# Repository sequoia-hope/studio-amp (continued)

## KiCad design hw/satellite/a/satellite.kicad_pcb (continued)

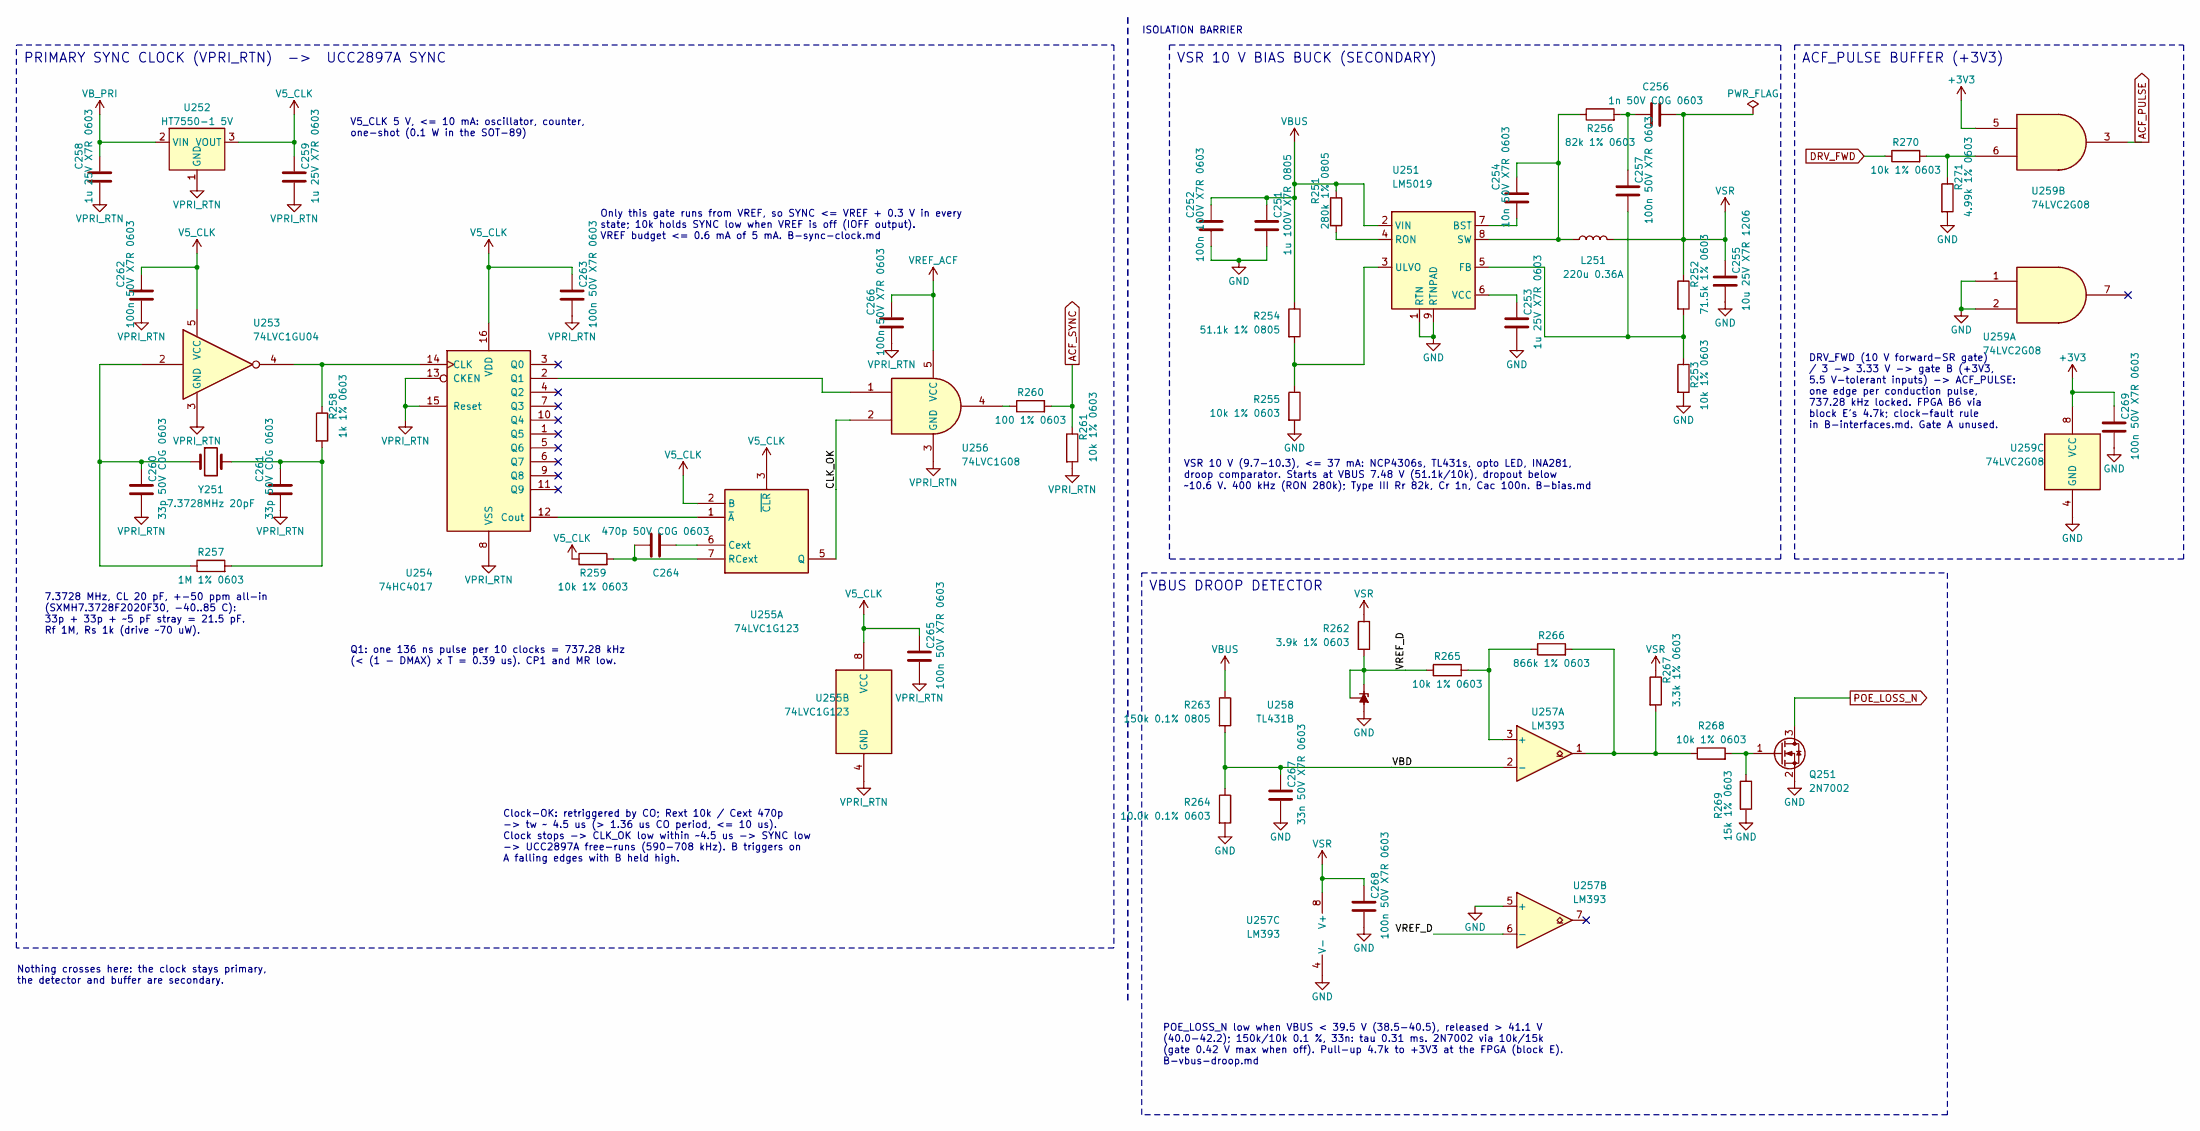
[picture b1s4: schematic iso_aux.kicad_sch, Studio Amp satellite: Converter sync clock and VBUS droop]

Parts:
C251: 1u 100V X7R 0805; C_0805_2012Metric; MPN HMK212BC7105KGHTE; LCSC C385977
C252: 100n 100V X7R 0603; C_0603_1608Metric; MPN CL10B104KC8NNNC; LCSC C15725
C253, C258, C259: 1u 25V X7R 0603; C_0603_1608Metric; MPN CL10B105KA8NNNC; LCSC C29936
C254: 10n 50V X7R 0603; C_0603_1608Metric; MPN CL10B103KB8NNNC; LCSC C1589
C255: 10u 25V X7R 1206; C_1206_3216Metric; MPN CL31B106KAHNNNE; LCSC C14860
C256: 1n 50V C0G 0603; C_0603_1608Metric; MPN CL10C102JB8NNNC; LCSC C163508
C257, C262, C263, C265, C266, C268, C269: 100n 50V X7R 0603; C_0603_1608Metric; MPN CL10B104KB8NNNC; LCSC C1591
C260, C261: 33p 50V C0G 0603; C_0603_1608Metric; MPN CL10C330JB8NNNC; LCSC C1663
C264: 470p 50V C0G 0603; C_0603_1608Metric; MPN CL10C471JB8NNNC; LCSC C27694
C267: 33n 50V X7R 0603; C_0603_1608Metric; MPN CL10B333KB8NNNC; LCSC C21117
L251: 220u 0.36A; L_SXN_SM5845; MPN SM5845-221MT; LCSC C10123
Q251: 2N7002; SOT-23; MPN 2N7002; LCSC C8545
R251: 280k 1% 0805; R_0805_2012Metric; MPN 0805W8F2803T5E; LCSC C17597
R252: 71.5k 1% 0603; R_0603_1608Metric; MPN 0603WAF7152T5E; LCSC C23103
R253, R255, R259, R261, R265, R268, R270: 10k 1% 0603; R_0603_1608Metric; MPN 0603WAF1002T5E; LCSC C25804
R254: 51.1k 1% 0805; R_0805_2012Metric; MPN 0805W8F5112T5E; LCSC C17731
R256: 82k 1% 0603; R_0603_1608Metric; MPN 0603WAF8202T5E; LCSC C23254
R257: 1M 1% 0603; R_0603_1608Metric; MPN 0603WAF1004T5E; LCSC C22935
R258: 1k 1% 0603; R_0603_1608Metric; MPN 0603WAF1001T5E; LCSC C21190
R260: 100 1% 0603; R_0603_1608Metric; MPN 0603WAF1000T5E; LCSC C22775
R262: 3.9k 1% 0603; R_0603_1608Metric; MPN 0603WAF3901T5E; LCSC C23018
R263: 150k 0.1% 0805; R_0805_2012Metric; MPN RT0805BRD07150KL; LCSC C136927
R264: 10.0k 0.1% 0603; R_0603_1608Metric; MPN RT0603BRD0710KL; LCSC C95204
R266: 866k 1% 0603; R_0603_1608Metric; MPN 0603WAF8663T5E; LCSC C23257
R267: 3.3k 1% 0603; R_0603_1608Metric; MPN 0603WAF3301T5E; LCSC C22978
R269: 15k 1% 0603; R_0603_1608Metric; MPN 0603WAF1502T5E; LCSC C22809
R271: 4.99k 1% 0603; R_0603_1608Metric; MPN 0603WAF4991T5E; LCSC C23046
U251: LM5019; SOIC-8-1EP_3.9x4.9mm_P1.27mm_EP2.95x4.9mm_Mask2.71x3.4mm; MPN LM5019MRX/NOPB; LCSC C471034
U252: HT7550-1 5V; SOT-89-3; MPN HT7550-1; LCSC C16106
U253: 74LVC1GU04; SOT-23-5; MPN SN74LVC1GU04DBVR; LCSC C81934
U254: 74HC4017; SOIC-16_3.9x9.9mm_P1.27mm; MPN 74HC4017D,653; LCSC C148206
U255: 74LVC1G123; SSOP-8_2.95x2.8mm_P0.65mm; MPN SN74LVC1G123DCTR; LCSC C123302
U256: 74LVC1G08; SOT-23-5; MPN SN74LVC1G08DBVR; LCSC C7666
U257: LM393; SOIC-8_3.9x4.9mm_P1.27mm; MPN LM393DR2G; LCSC C7955
U258: TL431B; SOT-23; MPN TL431BIDBZR; LCSC C41283
U259: 74LVC2G08; TSSOP-8_3x3mm_P0.65mm; MPN 74LVC2G08DP,125; LCSC C406037
Y251: 7.3728MHz 20pF; Crystal_SMD_HC49-SD; MPN SXMH7.3728F2020F30; LCSC C2901749

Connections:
/iso_aux/CLK_OK: U255.5 (Q), U256.2
/iso_aux/VBD: C267.1, R263.2, R264.1, U257.2 (-)
/iso_aux/VREF_D: R262.2, R265.1, U257.6 (-), U258.1 (K), U258.2 (REF)
ACF_PULSE: U259.3; also elsewhere on the board
ACF_SYNC: R260.2, R261.1; also elsewhere on the board
DRV_FWD: R270.1; also elsewhere on the board
unnamed: C256.1, C257.1, R256.2
unnamed: C260.1, R257.1, U253.2, Y251.1
unnamed: C261.1, R257.2, R258.2, Y251.2
unnamed: Q251.1 (G), R268.2, R269.1
unnamed: R260.1, U256.4
unnamed: R266.2, R267.2, R268.1, U257.1
unnamed: R270.2, R271.1, U259.6
unnamed: C254.2, U251.7 (BST)
unnamed: C257.2, R252.2, R253.1, U251.5 (FB)
unnamed: R251.2, U251.4 (RON)
unnamed: C254.1, L251.1, R256.1, U251.8 (SW)
unnamed: R254.2, R255.1, U251.3 (ULVO)
unnamed: C253.1, U251.6 (VCC)
unnamed: R258.1, U253.4, U254.14 (CLK)
unnamed: U254.12 (Cout), U255.1 (~A)
unnamed: U254.2 (Q1), U256.1
unnamed: C264.2, U255.6 (Cext)
unnamed: C264.1, R259.2, U255.7 (RCext)
unnamed: R265.2, R266.1, U257.3 (+)
POE_LOSS_N: Q251.3 (D); also elsewhere on the board
V5_CLK: C259.1, C262.1, C263.1, C265.1, R259.1, U252.3 (VOUT), U253.5 (VCC), U254.16 (VDD), U255.2 (B), U255.3 (~CLR), U255.8 (VCC)
VPRI_RTN: C258.2, C259.2, C260.2, C261.2, C262.2, C263.2, C265.2, C266.2, R261.2, U252.1 (GND), U253.3 (GND), U254.8 (VSS), U254.13 (CKEN), U254.15 (Reset), U255.4 (GND), U256.3 (GND); also elsewhere on the board
VREF_ACF: C266.1, U256.5 (VCC); also elsewhere on the board
VSR: C255.1, C256.2, C268.1, L251.2, R252.1, R262.1, R267.1, U257.8 (V+); also elsewhere on the board

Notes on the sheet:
V5_CLK 5 V, <= 10 mA: oscillator, counter, one-shot (0.1 W in the SOT-89)
7.3728 MHz, CL 20 pF, +-50 ppm all-in (SXMH7.3728F2020F30, -40..85 C): 33p + 33p + ~5 pF stray = 21.5 pF. Rf 1M, Rs 1k (drive ~70 uW).
Q1: one 136 ns pulse per 10 clocks = 737.28 kHz (< (1 - DMAX) x T = 0.39 us). CP1 and MR low.
Clock-OK: retriggered by CO; Rext 10k / Cext 470p -> tw ~ 4.5 us (> 1.36 us CO period, <= 10 us). Clock stops -> CLK_OK low within ~4.5 us -> SYNC low -> UCC2897A free-runs (590-708 kHz). B triggers on A falling edges with B held high.
Only this gate runs from VREF, so SYNC <= VREF + 0.3 V in every state; 10k holds SYNC low when VREF is off (IOFF output). VREF budget <= 0.6 mA of 5 mA. B-sync-clock.md
PRIMARY SYNC CLOCK (VPRI_RTN) -> UCC2897A SYNC
ISOLATION BARRIER
Nothing crosses here: the clock stays primary, the detector and buffer are secondary.
VSR 10 V (9.7-10.3), <= 37 mA: NCP4306s, TL431s, opto LED, INA281, droop comparator. Starts at VBUS 7.48 V (51.1k/10k), dropout below ~10.6 V. 400 kHz (RON 280k); Type III Rr 82k, Cr 1n, Cac 100n. B-bias.md
VSR 10 V BIAS BUCK (SECONDARY)
POE_LOSS_N low when VBUS < 39.5 V (38.5-40.5), released > 41.1 V (40.0-42.2); 150k/10k 0.1 %, 33n: tau 0.31 ms. 2N7002 via 10k/15k (gate 0.42 V max when off). Pull-up 4.7k to +3V3 at the FPGA (block E). B-vbus-droop.md
VBUS DROOP DETECTOR
DRV_FWD (10 V forward-SR gate) / 3 -> 3.33 V -> gate B (+3V3, 5.5 V-tolerant inputs) -> ACF_PULSE: one edge per conduction pulse, 737.28 kHz locked. FPGA B6 via block E's 4.7k; clock-fault rule in B-interfaces.md. Gate A unused.
ACF_PULSE BUFFER (+3V3)

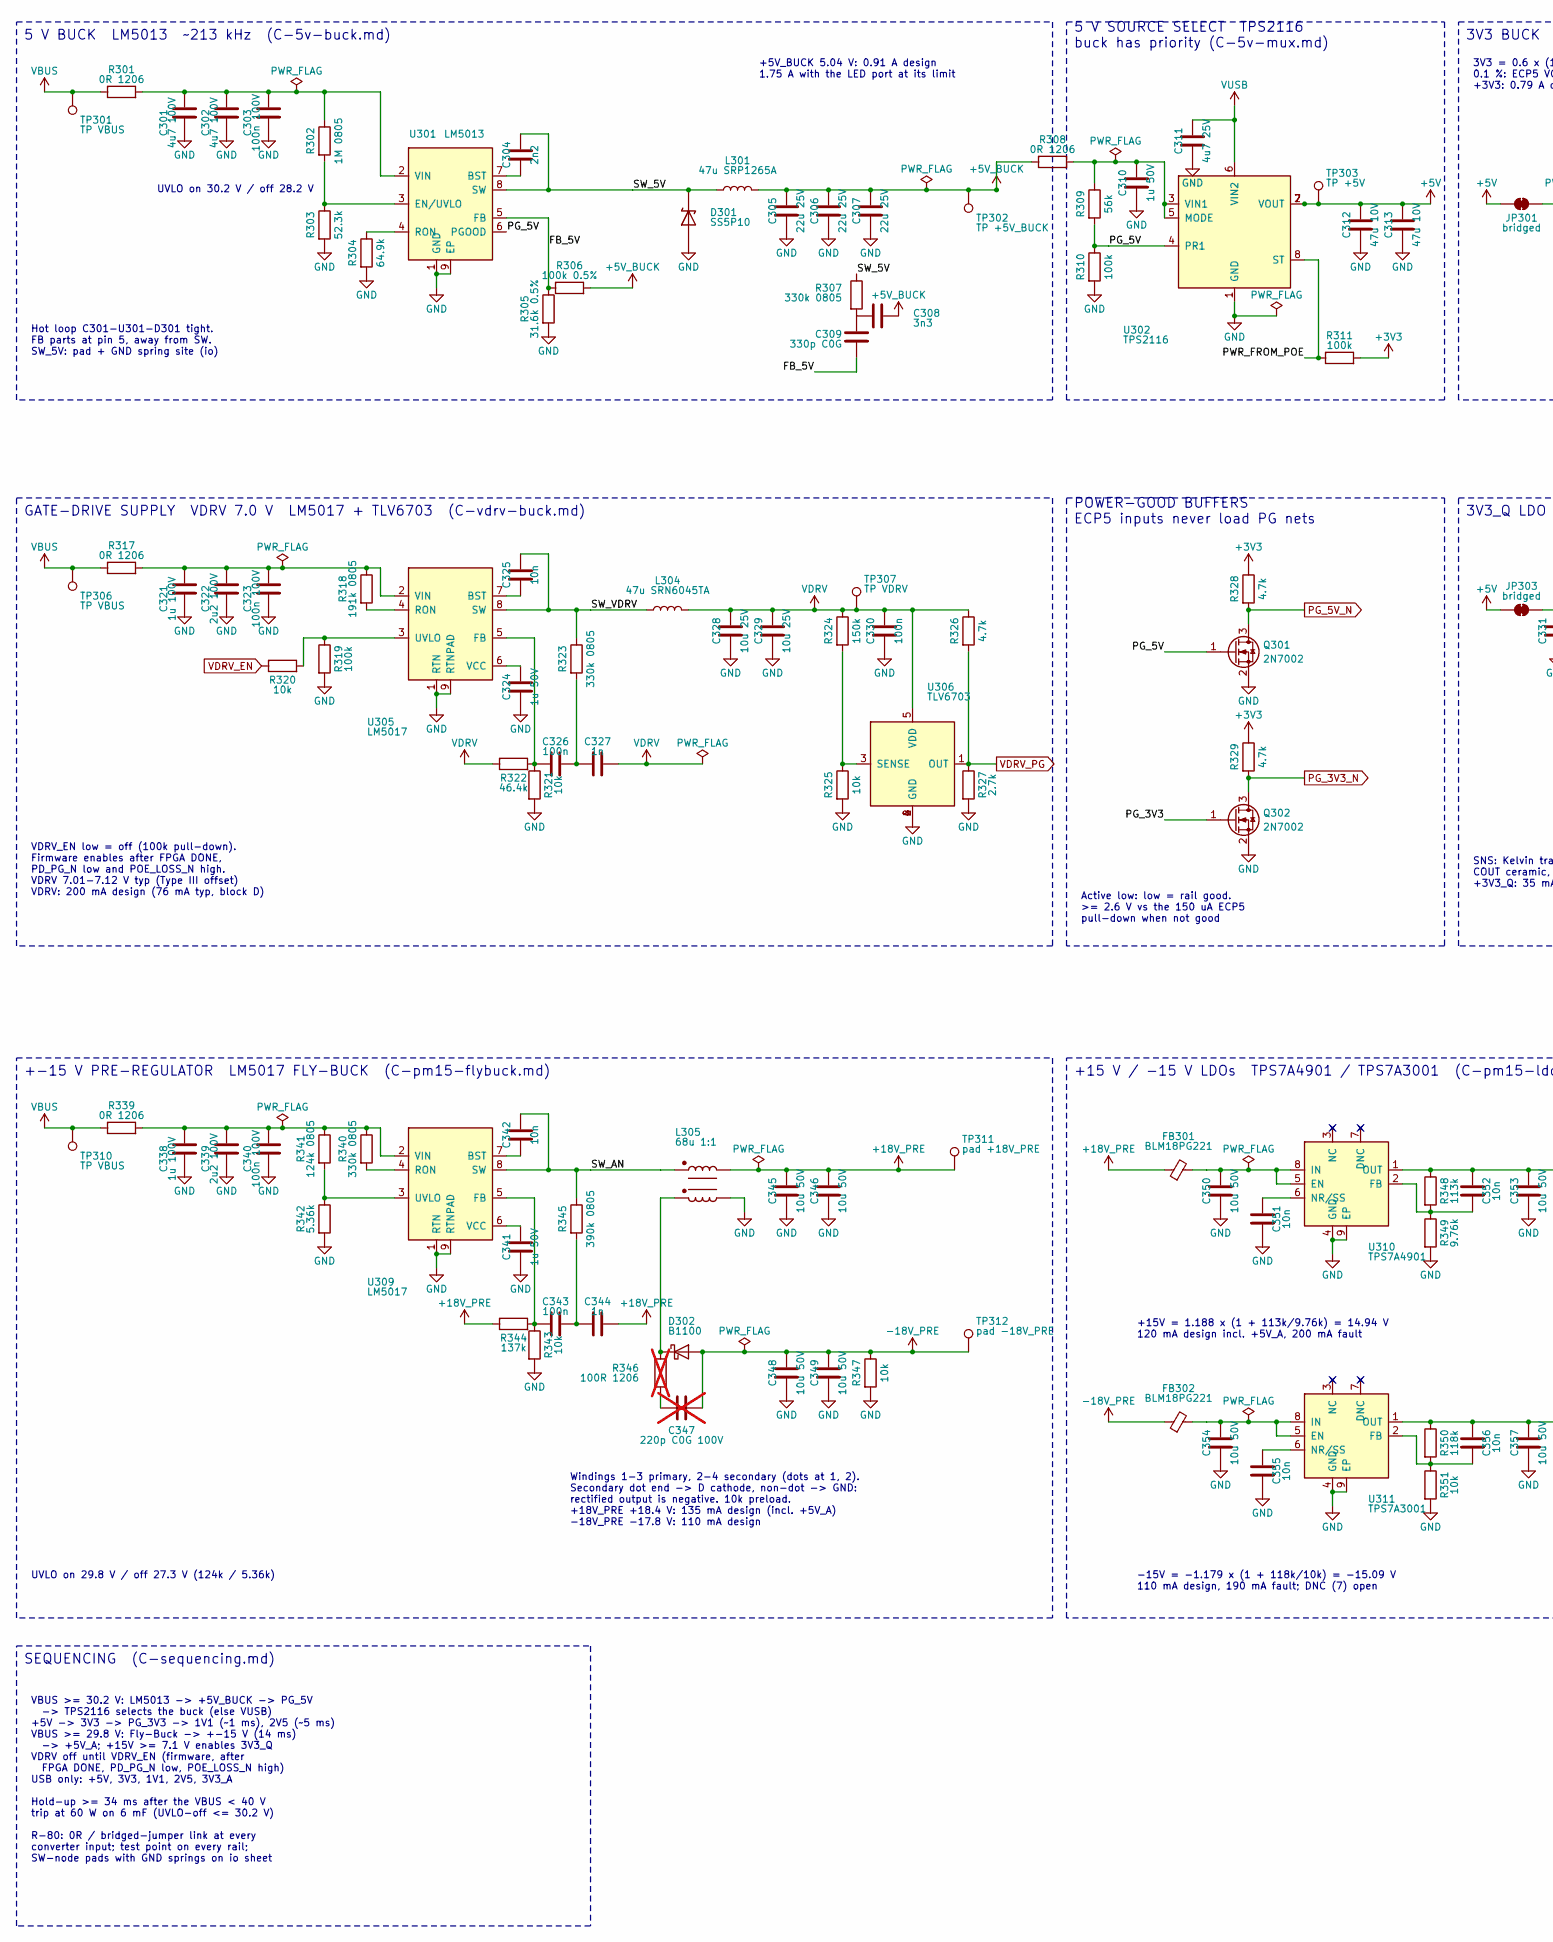
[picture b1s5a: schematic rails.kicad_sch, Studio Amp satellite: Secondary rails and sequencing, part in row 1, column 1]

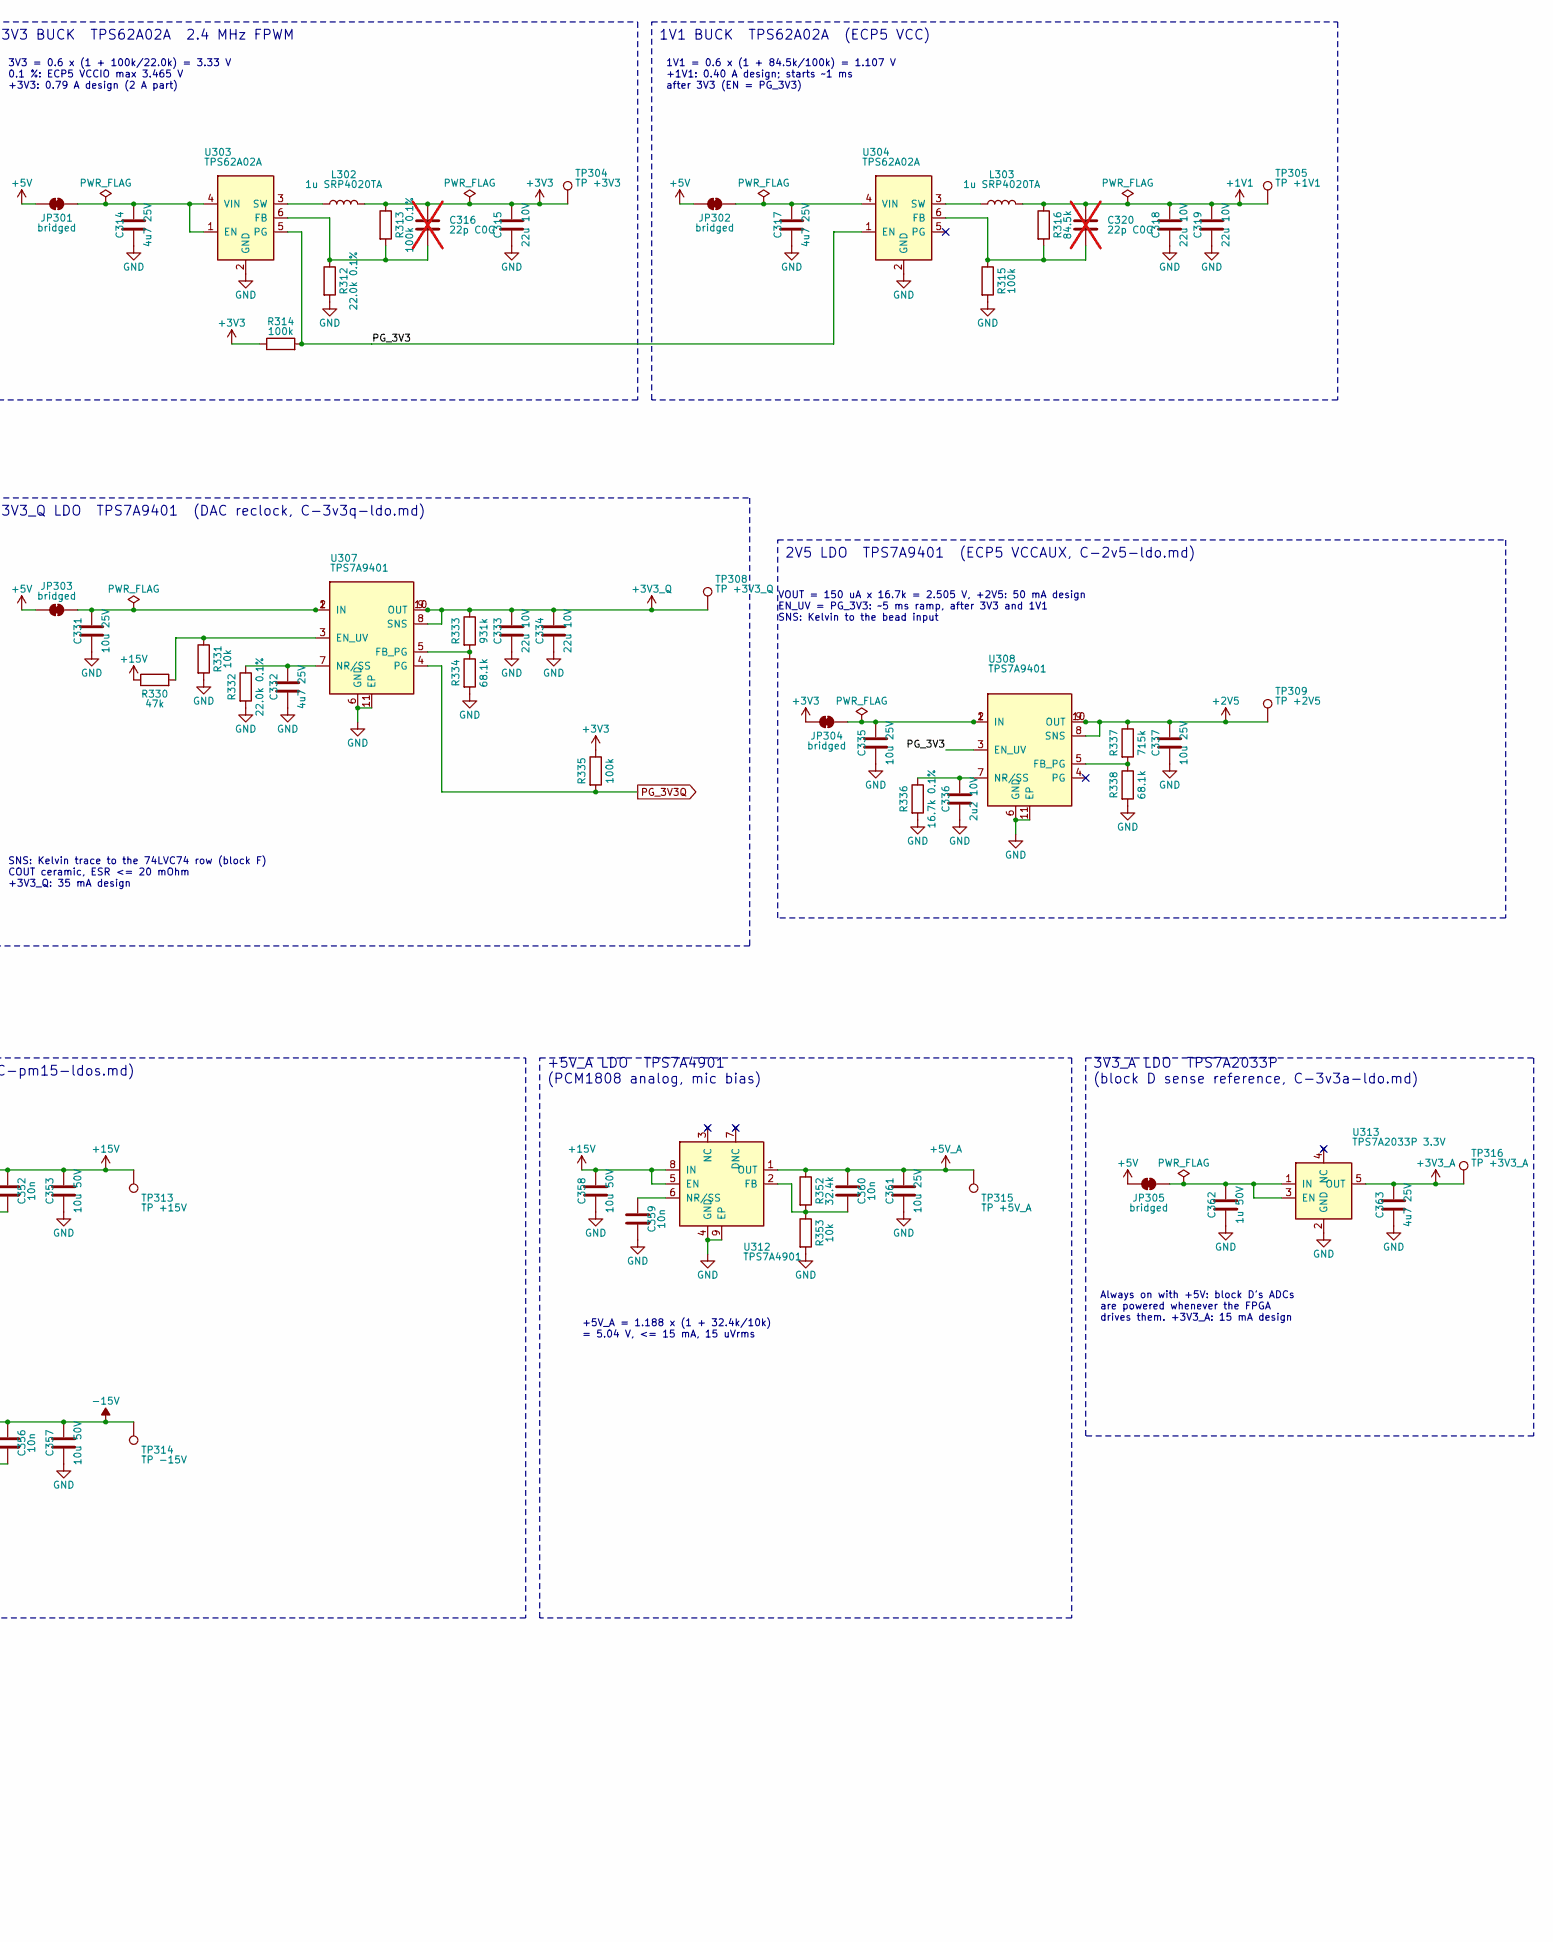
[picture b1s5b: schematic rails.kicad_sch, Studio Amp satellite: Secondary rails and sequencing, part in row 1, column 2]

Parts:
C301, C302: 4u7 100V; C_1210_3225Metric; MPN FS32X475K101EGG; LCSC C381466
C303, C323, C340: 100n 100V; C_0603_1608Metric; MPN 0603B104K101NT; LCSC C88219
C304: 2n2; C_0603_1608Metric; MPN 0603B222K500NT; LCSC C1604
C305, C306, C307: 22u 25V; C_1206_3216Metric; MPN CL31A226KAHNNNE; LCSC C12891
C308: 3n3; C_0603_1608Metric; MPN CL10B332KB8NNNC; LCSC C1613
C309: 330p C0G; C_0603_1608Metric; MPN CL10C331JB8NNNC; LCSC C1664
C310, C324, C341, C362: 1u 50V; C_0603_1608Metric; MPN CL10A105KB8NNNC; LCSC C15849
C311, C314, C317, C332, C363: 4u7 25V; C_0805_2012Metric; MPN CL21A475KAQNNNE; LCSC C1779
C312, C313: 47u 10V; C_1206_3216Metric; MPN CL31A476MPHNNNE; LCSC C96123
C315, C318, C319, C333, C334: 22u 10V; C_0805_2012Metric; MPN CL21A226MPQNNNE; LCSC C29277
C316, C320: 22p C0G; C_0603_1608Metric; MPN CL10C220JB8NNNC; LCSC C1653; not fitted
C321, C338: 1u 100V; C_1206_3216Metric; MPN CL31B105KCHNNNE; LCSC C13832
C322, C339: 2u2 100V; C_1210_3225Metric; MPN CL32B225KCJSNNE; LCSC C55151
C325, C342, C351, C352, C355, C356, C359, C360: 10n; C_0603_1608Metric; MPN 0603B103K500NT; LCSC C57112
C326, C330, C343: 100n; C_0603_1608Metric; MPN CC0603KRX7R9BB104; LCSC C14663
C327, C344: 1n; C_0603_1608Metric; MPN CL10B102KB8NNNC; LCSC C1588
C328, C329, C361: 10u 25V; C_1206_3216Metric; MPN CL31B106KAHNNNE; LCSC C14860
C331, C335, C337: 10u 25V; C_0805_2012Metric; MPN CL21A106KAYNNNE; LCSC C15850
C336: 2u2 10V; C_0603_1608Metric; MPN CC0603KRX7R6BB225; LCSC C513691
C345, C346, C348, C349, C350, C353, C354, C357: 10u 50V; C_1210_3225Metric; MPN UMK325AB7106KM-P; LCSC C337485
C347: 220p C0G 100V; C_0603_1608Metric; MPN AC0603JRNPO0BN221; LCSC C2982813; not fitted
C358: 10u 50V; C_1206_3216Metric; MPN CL31B106KBHNNNE; LCSC C89632
D301: SS5P10; TO-277A; MPN SS5P10-M3/86A; LCSC C46986
D302: B1100; D_SMA; MPN B1100-13-F; LCSC C110106
FB301, FB302: BLM18PG221; L_0603_1608Metric; MPN BLM18PG221SN1D; LCSC C80165
JP301, JP302, JP303, JP304, JP305: bridged; SolderJumper-2_P1.3mm_Bridged_RoundedPad1.0x1.5mm
L301: 47u SRP1265A; L_Bourns_SRP1265A; MPN SRP1265A-470M; LCSC C840530
L302, L303: 1u SRP4020TA; L_Bourns_SRP4020TA; MPN SRP4020TA-1R0M; LCSC C913245
L304: 47u SRN6045TA; L_Bourns_SRN6045TA; MPN SRN6045TA-470M; LCSC C5151734
L305: 68u 1:1; L_PROD_PSSCAQ7048; MPN PSSCAQ7048M-680M; LCSC C56266204
Q301, Q302: 2N7002; SOT-23; MPN 2N7002; LCSC C8545
R301, R308, R317, R339: 0R 1206; R_1206_3216Metric; MPN 1206W4F0000T5E; LCSC C17888
R302: 1M 0805; R_0805_2012Metric; MPN 0805W8F1004T5E; LCSC C17514
R303: 52.3k; R_0603_1608Metric; MPN 0603WAF5232T5E; LCSC C23198
R304: 64.9k; R_0603_1608Metric; MPN 0603WAF6492T5E; LCSC C14891
R305: 31.6k 0.5%; R_0603_1608Metric; MPN 0603WAD3162T5E; LCSC C423046
R306: 100k 0.5%; R_0603_1608Metric; MPN 0603WAD1003T5E; LCSC C423093
R307, R323, R340: 330k 0805; R_0805_2012Metric; MPN 0805W8F3303T5E; LCSC C17629
R309: 56k; R_0603_1608Metric; MPN 0603WAF5602T5E; LCSC C23206
R310, R311, R314, R315, R319, R335: 100k; R_0603_1608Metric; MPN 0603WAF1003T5E; LCSC C25803
R312, R332: 22.0k 0.1%; R_0603_1608Metric; MPN RT0603BRD0722KL; LCSC C469656
R313: 100k 0.1%; R_0603_1608Metric; MPN RT0603BRD07100KL; LCSC C122538
R316: 84.5k; R_0603_1608Metric; MPN 0603WAF8452T5E; LCSC C23118
R318: 191k 0805; R_0805_2012Metric; MPN 0805W8F1913T5E; LCSC C17511
R320, R321, R325, R331, R343, R347, R351, R353: 10k; R_0603_1608Metric; MPN 0603WAF1002T5E; LCSC C25804
R322: 46.4k; R_0603_1608Metric; MPN 0603WAF4642T5E; LCSC C23059
R324: 150k; R_0603_1608Metric; MPN 0603WAF1503T5E; LCSC C22807
R326, R328, R329: 4.7k; R_0603_1608Metric; MPN 0603WAF4701T5E; LCSC C23162
R327: 2.7k; R_0603_1608Metric; MPN 0603WAF2701T5E; LCSC C13167
R330: 47k; R_0603_1608Metric; MPN 0603WAF4702T5E; LCSC C25819
R333: 931k; R_0603_1608Metric; MPN 0603WAF9313T5E; LCSC C246847
R334, R338: 68.1k; R_0603_1608Metric; MPN 0603WAF6812T5E; LCSC C25976
R336: 16.7k 0.1%; R_0603_1608Metric; MPN RT0603BRD0716K7L; LCSC C861155
R337: 715k; R_0603_1608Metric; MPN 0603WAF7153T5E; LCSC C23237
R341: 124k 0805; R_0805_2012Metric; MPN 0805W8F1243T5E; LCSC C17440
R342: 5.36k; R_0603_1608Metric; MPN 0603WAF5361T5E; LCSC C25973
R344: 137k; R_0603_1608Metric; MPN 0603WAF1373T5E; LCSC C22872
R345: 390k 0805; R_0805_2012Metric; MPN 0805W8F3903T5E; LCSC C17656
R346: 100R 1206; R_1206_3216Metric; MPN 1206W4F1000T5E; LCSC C17901; not fitted
R348: 113k; R_0603_1608Metric; MPN 0603WAF1133T5E; LCSC C22862
R349: 9.76k; R_0603_1608Metric; MPN 0603WAF9761T5E; LCSC C23128
R350: 118k; R_0603_1608Metric; MPN 0603WAF1183T5E; LCSC C25806
R352: 32.4k; R_0603_1608Metric; MPN 0603WAF3242T5E; LCSC C13187
TP301, TP306, TP310: TP VBUS; TestPoint_Keystone_5015_Micro_Mini; MPN 5015; LCSC C2906768
TP302: TP +5V_BUCK; TestPoint_Keystone_5015_Micro_Mini; MPN 5015; LCSC C2906768
TP303: TP +5V; TestPoint_Keystone_5015_Micro_Mini; MPN 5015; LCSC C2906768
TP304: TP +3V3; TestPoint_Keystone_5015_Micro_Mini; MPN 5015; LCSC C2906768
TP305: TP +1V1; TestPoint_Keystone_5015_Micro_Mini; MPN 5015; LCSC C2906768
TP307: TP VDRV; TestPoint_Keystone_5015_Micro_Mini; MPN 5015; LCSC C2906768
TP308: TP +3V3_Q; TestPoint_Keystone_5015_Micro_Mini; MPN 5015; LCSC C2906768
TP309: TP +2V5; TestPoint_Keystone_5015_Micro_Mini; MPN 5015; LCSC C2906768
TP311: pad +18V_PRE; TestPoint_Pad_D1.0mm
TP312: pad -18V_PRE; TestPoint_Pad_D1.0mm
TP313: TP +15V; TestPoint_Keystone_5015_Micro_Mini; MPN 5015; LCSC C2906768
TP314: TP -15V; TestPoint_Keystone_5015_Micro_Mini; MPN 5015; LCSC C2906768
TP315: TP +5V_A; TestPoint_Keystone_5015_Micro_Mini; MPN 5015; LCSC C2906768
TP316: TP +3V3_A; TestPoint_Keystone_5015_Micro_Mini; MPN 5015; LCSC C2906768
U301: LM5013; TI_SO-PowerPAD-8; MPN LM5013DDAR; LCSC C5383001
U302: TPS2116; SOT-583-8; MPN TPS2116DRLR; LCSC C3235557
U303, U304: TPS62A02A; TSOT-23-6; MPN TPS62A02APDDCR; LCSC C25687169
U305, U309: LM5017; TI_SO-PowerPAD-8; MPN LM5017MRX/NOPB; LCSC C34355
U306: TLV6703; TSOT-23-6; MPN TLV6703DDCT; LCSC C2877614
U307, U308: TPS7A9401; Texas_DSC0010J; MPN TPS7A9401DSCR; LCSC C5220127
U310, U312: TPS7A4901; HVSSOP-8-1EP_3x3mm_P0.65mm_EP1.57x1.89mm; MPN TPS7A4901DGNR; LCSC C16430
U311: TPS7A3001; HVSSOP-8-1EP_3x3mm_P0.65mm_EP1.57x1.89mm; MPN TPS7A3001DGNR; LCSC C33835
U313: TPS7A2033P 3.3V; SOT-23-5; MPN TPS7A2033PDBVR; LCSC C2862740

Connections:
+2V5: C337.1, R337.1, TP309.1, U308.8 (SNS), U308.9 (OUT), U308.10 (OUT); also elsewhere on the board
+3V3_A: C363.1, TP316.1, U313.5 (OUT); also elsewhere on the board
+3V3_Q: C333.1, C334.1, R333.1, TP308.1, U307.8 (SNS), U307.9 (OUT), U307.10 (OUT); also elsewhere on the board
+5V: C312.1, C313.1, JP301.1 (A), JP302.1 (A), JP303.1 (A), JP305.1 (A), TP303.1, U302.2 (VOUT), U302.7 (VOUT); also elsewhere on the board
+5V_A: C360.1, C361.1, R352.1, TP315.1, U312.1 (OUT); also elsewhere on the board
+15V: C352.1, C353.1, C358.1, R330.1, R348.1, TP313.1, U310.1 (OUT), U312.5 (EN), U312.8 (IN); also elsewhere on the board
-15V: C356.1, C357.1, R350.1, TP314.1, U311.1 (OUT); also elsewhere on the board
/rails/FB_5V: C309.2, R305.1, R306.1, U301.5 (FB)
/rails/PG_3V3: Q302.1 (G), R314.2, U303.5 (PG), U304.1 (EN), U308.3 (EN_UV)
/rails/PG_5V: Q301.1 (G), R309.2, R310.1, U301.6 (PGOOD), U302.4 (PR1)
/rails/PWR_FROM_POE: R311.1, U302.8 (ST)
/rails/SW_5V: C304.1, D301.3 (K), L301.1, R307.1, U301.8 (SW)
/rails/SW_AN: C342.1, L305.1, R345.1, U309.8 (SW)
/rails/SW_VDRV: C325.1, L304.1, R323.1, U305.8 (SW)
unnamed: C308.1, C309.1, R307.2
unnamed: C326.2, C327.1, R323.2
unnamed: C343.2, C344.1, R345.2
unnamed: C347.1, R346.2
unnamed: D302.1 (K), L305.2, R346.1
unnamed: C304.2, U301.7 (BST)
unnamed: R302.2, R303.1, U301.3 (EN/UVLO)
unnamed: R304.1, U301.4 (RON)
unnamed: C316.2, R312.1, R313.2, U303.6 (FB)
unnamed: L302.1, U303.3 (SW)
unnamed: C320.2, R315.1, R316.2, U304.6 (FB)
unnamed: L303.1, U304.3 (SW)
unnamed: C325.2, U305.7 (BST)
unnamed: C326.1, R321.1, R322.2, U305.5 (FB)
unnamed: R318.2, U305.4 (RON)
unnamed: R319.1, R320.2, U305.3 (UVLO)
unnamed: C324.1, U305.6 (VCC)
unnamed: R324.2, R325.1, U306.3 (SENSE)
unnamed: R330.2, R331.1, U307.3 (EN_UV)
unnamed: R333.2, R334.1, U307.5 (FB_PG)
unnamed: C332.1, R332.1, U307.7 (NR/SS)
unnamed: R337.2, R338.1, U308.5 (FB_PG)
unnamed: C336.1, R336.1, U308.7 (NR/SS)
unnamed: C342.2, U309.7 (BST)
unnamed: C343.1, R343.1, R344.2, U309.5 (FB)
unnamed: R340.2, U309.4 (RON)
unnamed: R341.2, R342.1, U309.3 (UVLO)
unnamed: C341.1, U309.6 (VCC)
unnamed: C352.2, R348.2, R349.1, U310.2 (FB)
unnamed: C351.1, U310.6 (NR/SS)
unnamed: C356.2, R350.2, R351.1, U311.2 (FB)
unnamed: C355.1, U311.6 (NR/SS)
unnamed: C360.2, R352.2, R353.1, U312.2 (FB)
unnamed: C359.1, U312.6 (NR/SS)
PG_3V3Q: R335.2, U307.4 (PG); also elsewhere on the board
PG_3V3_N: Q302.3 (D), R329.2; also elsewhere on the board
PG_5V_N: Q301.3 (D), R328.2; also elsewhere on the board
VDRV_EN: R320.1; also elsewhere on the board
VDRV_PG: R326.2, R327.1, U306.1 (OUT); also elsewhere on the board

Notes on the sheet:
5 V BUCK LM5013 ~213 kHz (C-5v-buck.md)
+5V_BUCK 5.04 V: 0.91 A design 1.75 A with the LED port at its limit
Hot loop C301-U301-D301 tight. FB parts at pin 5, away from SW. SW_5V: pad + GND spring site (io)
UVLO on 30.2 V / off 28.2 V
5 V SOURCE SELECT TPS2116 buck has priority (C-5v-mux.md)
3V3 BUCK TPS62A02A 2.4 MHz FPWM
3V3 = 0.6 x (1 + 100k/22.0k) = 3.33 V 0.1 %: ECP5 VCCIO max 3.465 V +3V3: 0.79 A design (2 A part)
1V1 BUCK TPS62A02A (ECP5 VCC)
1V1 = 0.6 x (1 + 84.5k/100k) = 1.107 V +1V1: 0.40 A design; starts ~1 ms after 3V3 (EN = PG_3V3)
GATE-DRIVE SUPPLY VDRV 7.0 V LM5017 + TLV6703 (C-vdrv-buck.md)
VDRV_EN low = off (100k pull-down). Firmware enables after FPGA DONE, PD_PG_N low and POE_LOSS_N high. VDRV 7.01-7.12 V typ (Type III offset) VDRV: 200 mA design (76 mA typ, block D)
POWER-GOOD BUFFERS ECP5 inputs never load PG nets
Active low: low = rail good. >= 2.6 V vs the 150 uA ECP5 pull-down when not good
3V3_Q LDO TPS7A9401 (DAC reclock, C-3v3q-ldo.md)
SNS: Kelvin trace to the 74LVC74 row (block F) COUT ceramic, ESR <= 20 mOhm +3V3_Q: 35 mA design
2V5 LDO TPS7A9401 (ECP5 VCCAUX, C-2v5-ldo.md)
VOUT = 150 uA x 16.7k = 2.505 V, +2V5: 50 mA design EN_UV = PG_3V3: ~5 ms ramp, after 3V3 and 1V1 SNS: Kelvin to the bead input
+-15 V PRE-REGULATOR LM5017 FLY-BUCK (C-pm15-flybuck.md)
Windings 1-3 primary, 2-4 secondary (dots at 1, 2). Secondary dot end -> D cathode, non-dot -> GND: rectified output is negative. 10k preload. +18V_PRE +18.4 V: 135 mA design (incl. +5V_A) -18V_PRE -17.8 V: 110 mA design
UVLO on 29.8 V / off 27.3 V (124k / 5.36k)
+15 V / -15 V LDOs TPS7A4901 / TPS7A3001 (C-pm15-ldos.md)
+15V = 1.188 x (1 + 113k/9.76k) = 14.94 V 120 mA design incl. +5V_A, 200 mA fault
-15V = -1.179 x (1 + 118k/10k) = -15.09 V 110 mA design, 190 mA fault; DNC (7) open
+5V_A LDO TPS7A4901 (PCM1808 analog, mic bias)
+5V_A = 1.188 x (1 + 32.4k/10k) = 5.04 V, <= 15 mA, 15 uVrms
3V3_A LDO TPS7A2033P (block D sense reference, C-3v3a-ldo.md)
Always on with +5V: block D's ADCs are powered whenever the FPGA drives them. +3V3_A: 15 mA design
SEQUENCING (C-sequencing.md)
VBUS >= 30.2 V: LM5013 -> +5V_BUCK -> PG_5V -> TPS2116 selects the buck (else VUSB) +5V -> 3V3 -> PG_3V3 -> 1V1 (~1 ms), 2V5 (~5 ms) VBUS >= 29.8 V: Fly-Buck -> +-15 V (14 ms) -> +5V_A; +15V >= 7.1 V enables 3V3_Q VDRV off until VDRV_EN (firmware, after FPGA DONE, PD_PG_N low, POE_LOSS_N high) USB 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
